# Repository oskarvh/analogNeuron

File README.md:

# analogNeuron
Design doc for an analog neural network (perceptron) built using discrete components.

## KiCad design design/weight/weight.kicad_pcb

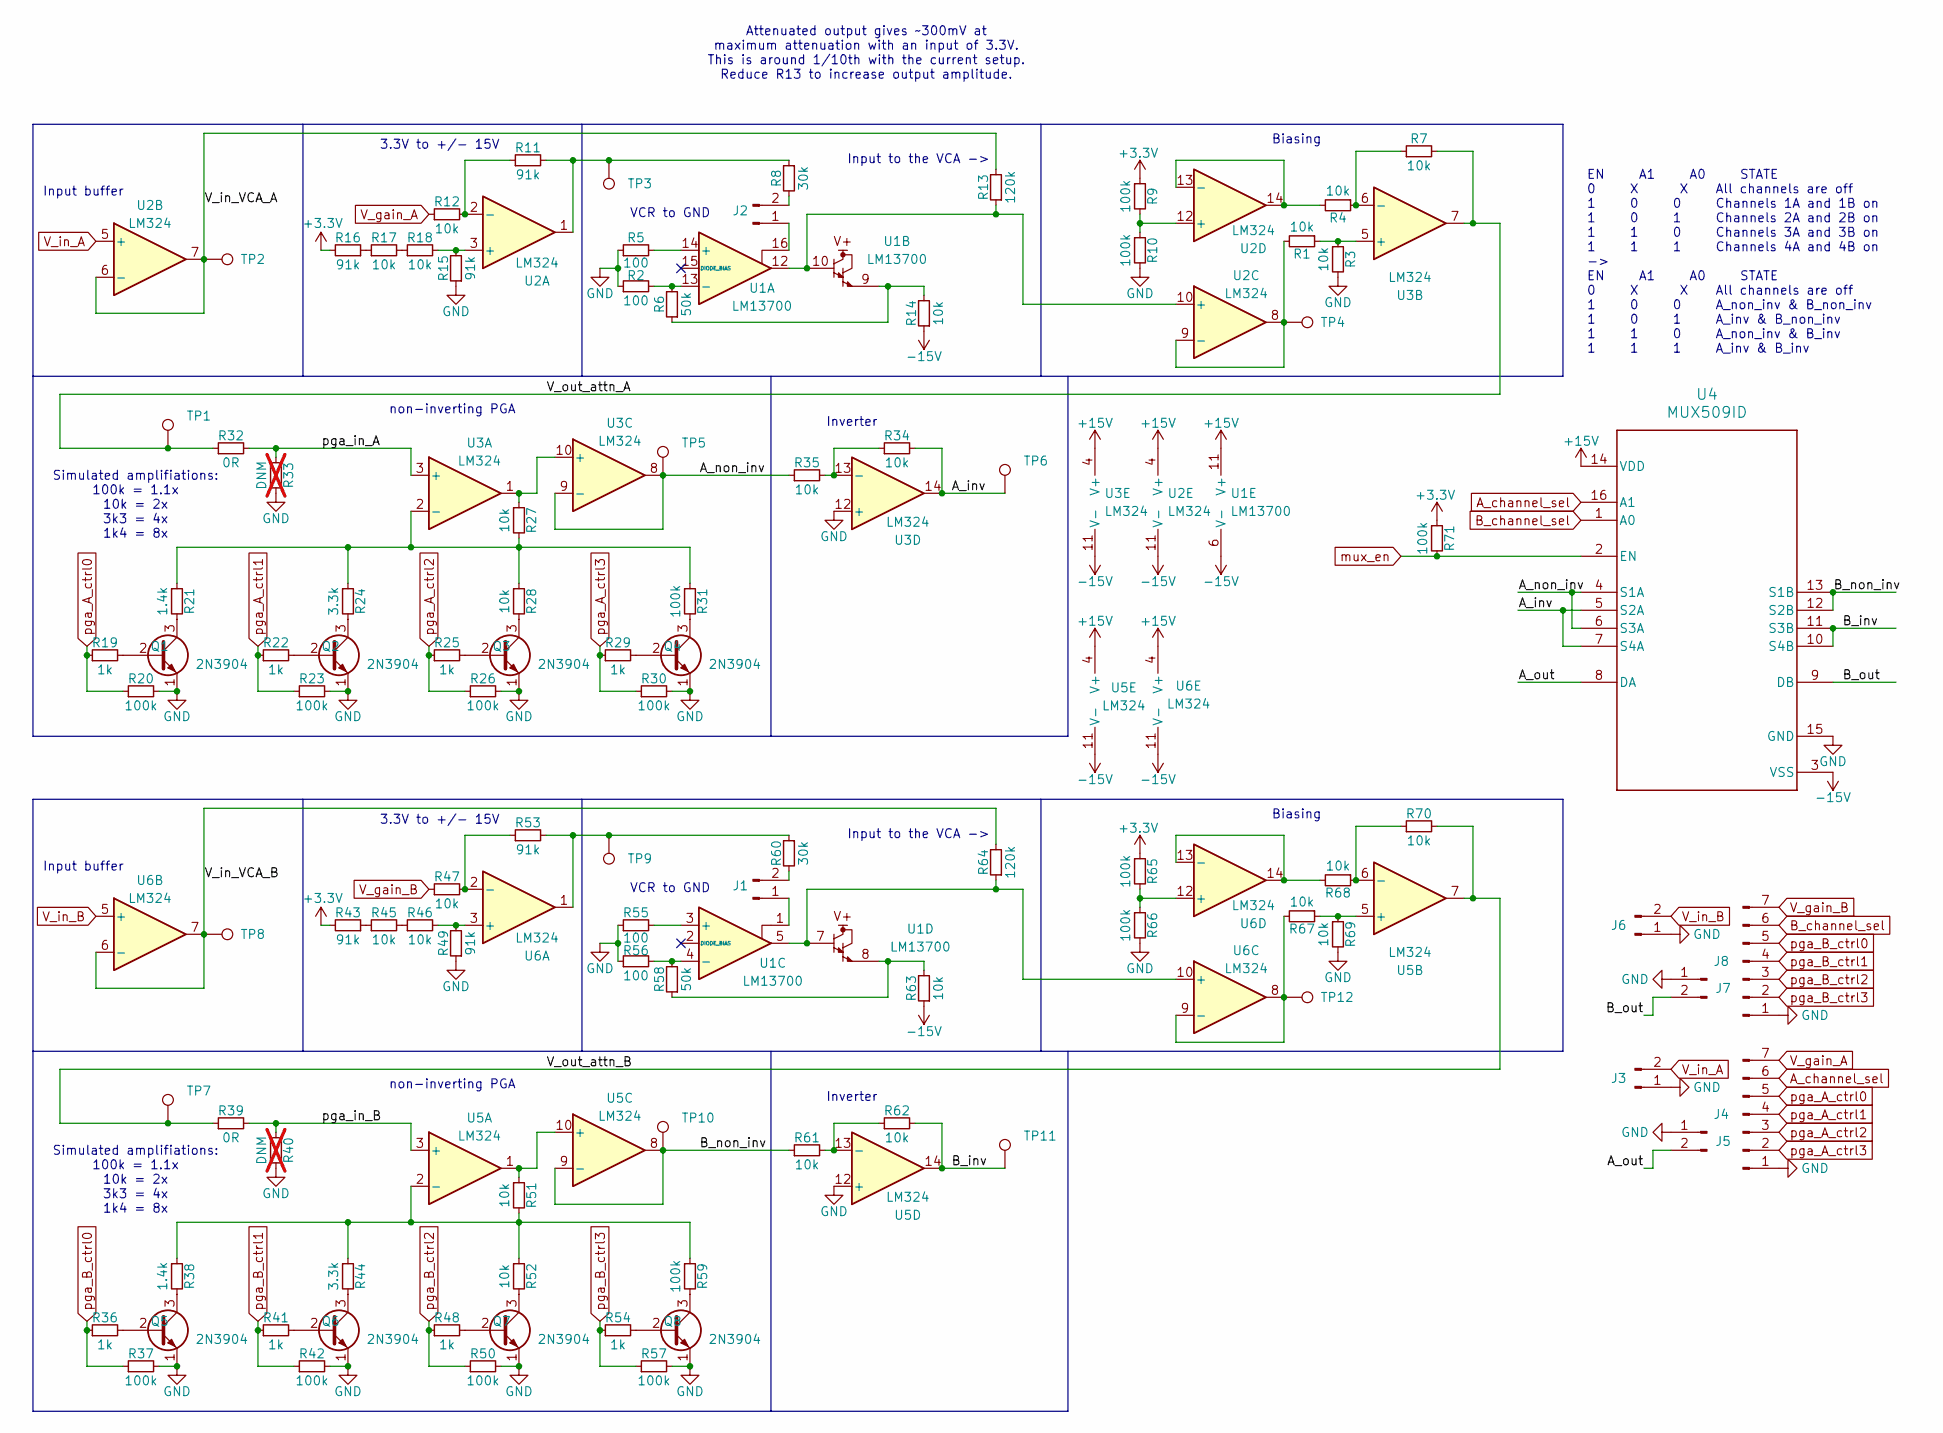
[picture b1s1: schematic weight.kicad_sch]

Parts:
J1, J2, J3, J5, J6, J7: Conn_01x02_Pin; PinHeader_1x02_P2.54mm_Vertical
J4, J8: Conn_01x07_Pin; PinHeader_1x07_P2.54mm_Vertical
Q1, Q2, Q3, Q4, Q5, Q6, Q7, Q8: 2N3904; TO-92_Inline
R1, R3, R4, R7, R12, R14, R17, R18, R27, R28, R34, R35, R45, R46, R47, R51, R52, R61, R62, R63, R67, R68, R69, R70: 10k; R_0402_1005Metric
R2, R5, R55, R56: 100; R_0402_1005Metric
R6, R58: 50k; R_0402_1005Metric
R8, R60: 30k; R_0402_1005Metric
R9, R10, R20, R23, R26, R30, R31, R37, R42, R50, R57, R59, R65, R66, R71: 100k; R_0402_1005Metric
R11, R15, R16, R43, R49, R53: 91k; R_0402_1005Metric
R13, R64: 120k; R_0402_1005Metric
R19, R22, R25, R29, R36, R41, R48, R54: 1k; R_0402_1005Metric
R21, R38: 1.4k; R_0402_1005Metric
R24, R44: 3.3k; R_0402_1005Metric
R32, R39: 0R; R_0402_1005Metric
R33, R40: DNM; R_0402_1005Metric; not fitted
TP1, TP2, TP3, TP4, TP5, TP6, TP7, TP8, TP9, TP10, TP11, TP12: TestPoint; PinHeader_1x01_P2.54mm_Vertical
U1: LM13700; SOIC-16_3.9x9.9mm_P1.27mm
U2, U3, U5, U6: LM324; SOIC127P600X175-14N
U4: MUX509ID; D0016A_N

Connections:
+3.3V: R9.1, R16.2, R43.2, R65.1, R71.1
+15V: U1.11 (V+), U2.4 (V+), U3.4 (V+), U4.14 (VDD), U5.4 (V+), U6.4 (V+)
-15V: R14.1, R63.1, U1.6 (V-), U2.11 (V-), U3.11 (V-), U4.3 (VSS), U5.11 (V-), U6.11 (V-)
/A_inv: R34.2, TP6.1, U3.14, U4.5 (S2A), U4.7 (S4A)
/A_non_inv: R35.1, TP5.1, U3.8, U3.9 (-), U4.4 (S1A), U4.6 (S3A)
/A_out: J5.2, U4.8 (DA)
/B_inv: R62.2, TP11.1, U4.10 (S4B), U4.11 (S3B), U5.14
/B_non_inv: R61.1, TP10.1, U4.12 (S2B), U4.13 (S1B), U5.8, U5.9 (-)
/B_out: J7.2, U4.9 (DB)
/V_in_VCA_A: R13.2, TP2.1, U2.6 (-), U2.7
/V_in_VCA_B: R64.2, TP8.1, U6.6 (-), U6.7
/V_out_attn_A: R7.2, R32.1, TP1.1, U3.7
/V_out_attn_B: R39.1, R70.2, TP7.1, U5.7
/pga_in_A: R32.2, R33.1, U3.3 (+)
/pga_in_B: R39.2, R40.1, U5.3 (+)
A_channel_sel: J4.6, U4.16 (A1)
B_channel_sel: J8.6, U4.1 (A0)
GND: J3.1, J4.1, J5.1, J6.1, J7.1, J8.1, Q1.1 (E), Q2.1 (E), Q3.1 (E), Q4.1 (E), Q5.1 (E), Q6.1 (E), Q7.1 (E), Q8.1 (E), R2.1, R3.2, R5.1, R10.2, R15.1, R20.2, R23.2, R26.2, R30.2, R33.2, R37.2, R40.2, R42.2, R49.1, R50.2, R55.1, R56.1, R57.2, R66.2, R69.2, U3.12 (+), U4.15 (GND), U5.12 (+)
unnamed: J1.1, U1.1
unnamed: J1.2, R60.2
unnamed: J2.1, U1.16
unnamed: J2.2, R8.2
unnamed: Q1.2 (B), R19.2
unnamed: Q1.3 (C), R21.2
unnamed: Q2.2 (B), R22.2
unnamed: Q2.3 (C), R24.2
unnamed: Q3.2 (B), R25.2
unnamed: Q3.3 (C), R28.2
unnamed: Q4.2 (B), R29.2
unnamed: Q4.3 (C), R31.2
unnamed: Q5.2 (B), R36.2
unnamed: Q5.3 (C), R38.2
unnamed: Q6.2 (B), R41.2
unnamed: Q6.3 (C), R44.2
unnamed: Q7.2 (B), R48.2
unnamed: Q7.3 (C), R52.2
unnamed: Q8.2 (B), R54.2
unnamed: Q8.3 (C), R59.2
unnamed: R8.1, R11.2, TP3.1, U2.1
unnamed: R6.1, R14.2, U1.9
unnamed: R16.1, R17.1
unnamed: R17.2, R18.1
unnamed: R43.1, R45.1
unnamed: R45.2, R46.1
unnamed: R53.2, R60.1, TP9.1, U6.1
unnamed: R58.1, R63.2, U1.8
unnamed: R5.2, U1.14 (+)
unnamed: R2.2, R6.2, U1.13 (-)
unnamed: R55.2, U1.3 (+)
unnamed: R56.2, R58.2, U1.4 (-)
unnamed: R15.2, R18.2, U2.3 (+)
unnamed: R11.1, R12.2, U2.2 (-)
unnamed: R13.1, U1.10, U1.12, U2.10 (+)
unnamed: R1.2, TP4.1, U2.8, U2.9 (-)
unnamed: R9.2, R10.1, U2.12 (+)
unnamed: R4.2, U2.13 (-), U2.14
unnamed: R21.1, R24.1, R27.2, R28.1, R31.1, U3.2 (-)
unnamed: R1.1, R3.1, U3.5 (+)
unnamed: R4.1, R7.1, U3.6 (-)
unnamed: R27.1, U3.1, U3.10 (+)
unnamed: R34.1, R35.2, U3.13 (-)
unnamed: R38.1, R44.1, R51.2, R52.1, R59.1, U5.2 (-)
unnamed: R67.1, R69.1, U5.5 (+)
unnamed: R68.1, R70.1, U5.6 (-)
unnamed: R51.1, U5.1, U5.10 (+)
unnamed: R61.2, R62.1, U5.13 (-)
unnamed: R46.2, R49.2, U6.3 (+)
unnamed: R47.2, R53.1, U6.2 (-)
unnamed: R64.1, U1.5, U1.7, U6.10 (+)
unnamed: R67.2, TP12.1, U6.8, U6.9 (-)
unnamed: R65.2, R66.1, U6.12 (+)
unnamed: R68.2, U6.13 (-), U6.14
V_gain_A: J4.7, R12.1
V_gain_B: J8.7, R47.1
V_in_A: J3.2, U2.5 (+)
V_in_B: J6.2, U6.5 (+)
mux_en: R71.2, U4.2 (EN)
pga_A_ctrl0: J4.5, R19.1, R20.1
pga_A_ctrl1: J4.4, R22.1, R23.1
pga_A_ctrl2: J4.3, R25.1, R26.1
pga_A_ctrl3: J4.2, R29.1, R30.1
pga_B_ctrl0: J8.5, R36.1, R37.1
pga_B_ctrl1: J8.4, R41.1, R42.1
pga_B_ctrl2: J8.3, R48.1, R50.1
pga_B_ctrl3: J8.2, R54.1, R57.1

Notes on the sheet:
Input to the VCA ->
3.3V to +/- 15V
Inverter
VCR to GND
Biasing
Simulated amplifiations: 100k = 1.1x 10k = 2x 3k3 = 4x 1k4 = 8x
Attenuated output gives ~300mV at maximum attenuation with an input of 3.3V. This is around 1/10th with the current setup. Reduce R13 to increase output amplitude.
EN A1 A0 STATE 0 X X All channels are off 1 0 0 Channels 1A and 1B on 1 0 1 Channels 2A and 2B on 1 1 0 Channels 3A and 3B on 1 1 1 Channels 4A and 4B on -> EN A1 A0 STATE 0 X X All channels are off 1 0 0 A_non_inv & B_non_inv 1 0 1 A_inv & B_non_inv 1 1 0 A_non_inv & B_inv 1 1 1 A_inv & B_inv
non-inverting PGA
Input buffer

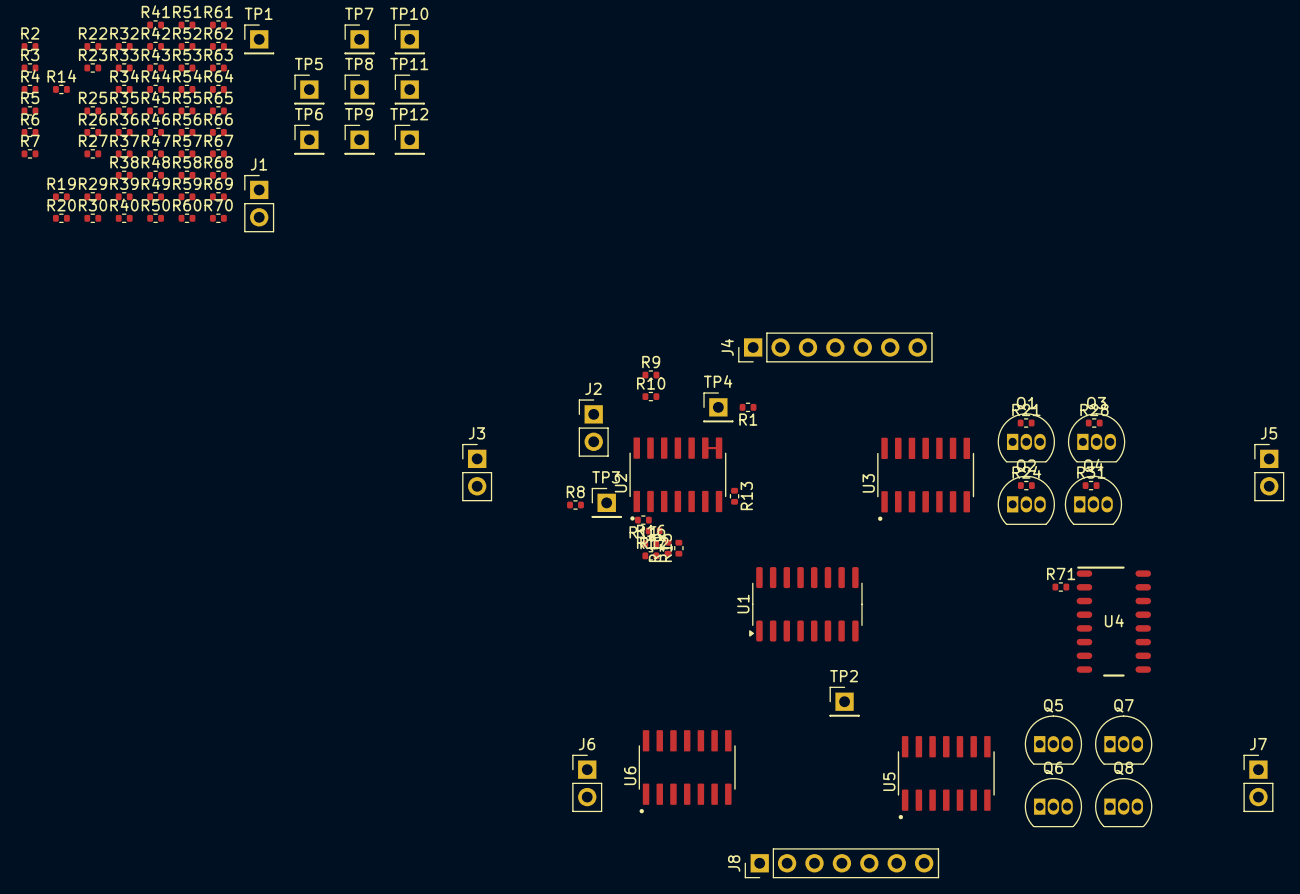
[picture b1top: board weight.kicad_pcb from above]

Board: 2 copper layers, 105 parts (0 on the bottom side), 85 nets.

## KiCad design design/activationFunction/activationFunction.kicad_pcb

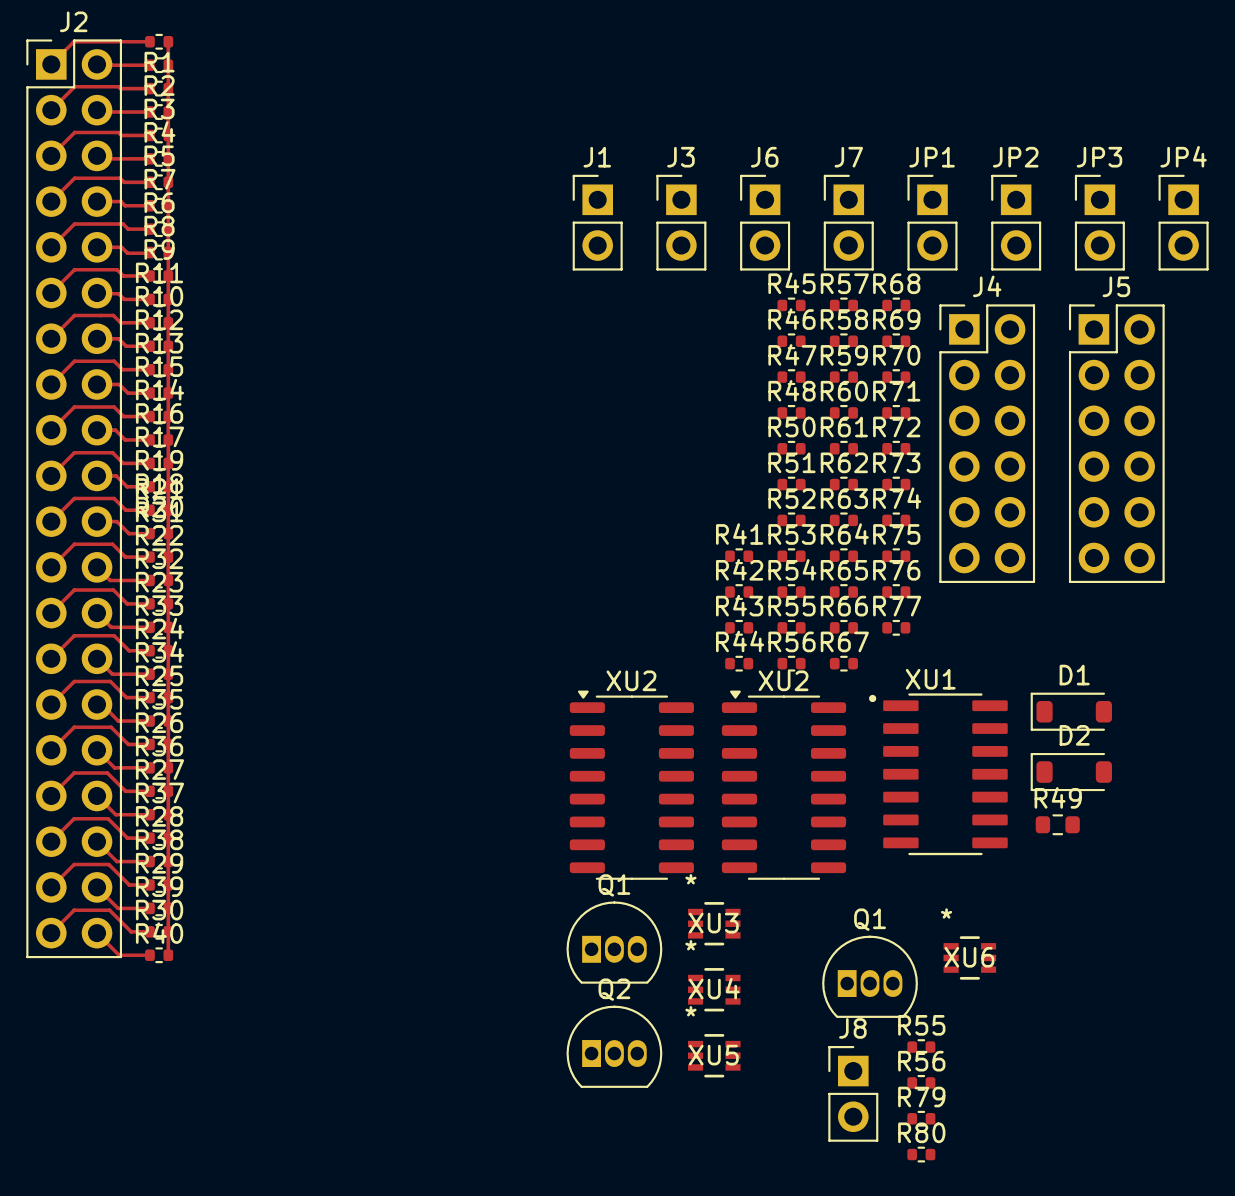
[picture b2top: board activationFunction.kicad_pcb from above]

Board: 2 copper layers, 105 parts (0 on the bottom side), 89 nets.

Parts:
D1, D2: 1N4148WGW; D_SOD-123
J1, J3, J6, J7, J8: Conn_01x02_Pin; PinHeader_1x02_P2.54mm_Vertical
J2: Conn_02x20_Counter_Clockwise; PinHeader_2x20_P2.54mm_Vertical
J4, J5: Conn_02x06_Counter_Clockwise; PinHeader_2x06_P2.54mm_Vertical
JP1, JP2, JP3, JP4: Jumper_2_Small_Open; PinHeader_1x02_P2.54mm_Vertical
Q1, Q1#2, Q2: 2N3904; TO-92_Inline
R1, R2, R3, R4, R5, R6, R7, R8, R9, R10, R11, R12, R13, R14, R15, R16, R17, R18, R19, R20, R21, R22, R23, R24, R25, R26, R27, R28, R29, R30, R31, R32, R33, R34, R35, R36, R37, R38, R39, R40, R41, R46, R50, R54, R55, R55#2, R56, R56#2, R57, R58, R60, R61: 100k; R_0402_1005Metric
R42, R51, R52, R53, R59: 1k; R_0402_1005Metric
R43: 35k; R_0402_1005Metric
R44: 5k; R_0402_1005Metric
R45, R63, R64, R66, R69, R70, R71, R72, R73: 10k; R_0402_1005Metric
R47, R48, R79, R80: 33k; R_0402_1005Metric
R49: 500k; R_0603_1608Metric
R62: 15k; R_0402_1005Metric
R65, R67, R68, R74, R75, R76: 91k; R_0402_1005Metric
R77: 0; R_0402_1005Metric
XU1: LM324; SOIC127P600X175-14N
XU2, XU2#2: LM13700; SOIC-16_3.9x9.9mm_P1.27mm
XU3, XU4, XU5, XU6: SSM6N7002CFU_LF; SOT-363 US6_TOS

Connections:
0: J3.1, J4.4, J4.9, J5.4, J5.9, J6.1, J7.1, R41.1, R49.1, R55.1, R68.1, R75.1, XU2.10, XU2.12, XU2#2.10, XU2#2.12, XU3.5, XU6.5
3.3V: J4.3, J4.10, J5.3, J5.10, R70.1, R71.1
+15V: D2.2 (A), J4.1, J4.12, J5.1, J5.12, Q1.3 (C), Q2.3 (C), XU1.4 (V+), XU2.11 (V+), XU2#2.11 (V+)
-15V: J4.2, J4.11, J5.2, J5.11, R51.2, R52.2, R53.2, R63.1, R64.1, XU1.11 (V-), XU2.6 (V-), XU2#2.6 (V-), XU5.5, XU6.2
/V_bias_l: J7.2, R73.1
/V_diff_n: Q2.2 (B), R48.2, XU3.3 (4)
/V_diff_out: Q2.1 (E), R54.1
/V_diff_p: R47.2, XU3.6 (1)
/V_in: R1.1, R2.1, R3.1, R4.1, R5.1, R6.1, R7.1, R8.1, R9.1, R10.1, R11.1, R12.1, R13.1, R14.1, R15.1, R16.1, R17.1, R18.1, R19.1, R20.1, R21.2, R22.2, R23.2, R24.2, R25.2, R26.2, R27.2, R28.2, R29.2, R30.2, R31.2, R32.2, R33.2, R34.2, R35.2, R36.2, R37.2, R38.2, R39.2, R40.2, R58.2, XU1.3 (+)
/V_out: J3.2, R56.2, R56#2.2, XU1.7
/V_sink: J1.2, XU4.3 (4)
/V_slope_l: J6.2, R66.1
/V_sum: R42.1, R43.2, R44.1, R45.1, R46.1, XU1.1
/V_sum_bias: R43.1, XU2.5, XU2.7, XU2#2.5, XU2#2.7, XU3.2
/out_bias: Q1.2 (B), R80.2, XU6.3 (4)
unnamed: D1.2 (A), D2.1 (K)
unnamed: D1.1 (K), Q1#2.3 (C), R47.1, R48.1, R50.1, R79.1, R80.1
unnamed: J1.1, R77.1, XU3.1 (3), XU3.4 (6)
unnamed: J2.1, R1.2
unnamed: J2.2, R2.2
unnamed: J2.3, R3.2
unnamed: J2.4, R4.2
unnamed: J2.5, R5.2
unnamed: J2.6, R7.2
unnamed: J2.7, R6.2
unnamed: J2.8, R8.2
unnamed: J2.9, R9.2
unnamed: J2.10, R11.2
unnamed: J2.11, R10.2
unnamed: J2.12, R12.2
unnamed: J2.13, R13.2
unnamed: J2.14, R15.2
unnamed: J2.15, R14.2
unnamed: J2.16, R16.2
unnamed: J2.17, R17.2
unnamed: J2.18, R19.2
unnamed: J2.19, R18.2
unnamed: J2.20, R20.2
unnamed: J2.21, R21.1
unnamed: J2.22, R31.1
unnamed: J2.23, R22.1
unnamed: J2.24, R32.1
unnamed: J2.25, R23.1
unnamed: J2.26, R33.1
unnamed: J2.27, R24.1
unnamed: J2.28, R34.1
unnamed: J2.29, R25.1
unnamed: J2.30, R35.1
unnamed: J2.31, R26.1
unnamed: J2.32, R36.1
unnamed: J2.33, R27.1
unnamed: J2.34, R37.1
unnamed: J2.35, R28.1
unnamed: J2.36, R38.1
unnamed: J2.37, R29.1
unnamed: J2.38, R39.1
unnamed: J2.39, R30.1
unnamed: J2.40, R40.1
unnamed: J8.1, XU6.1 (3), XU6.4 (6)
unnamed: J8.2, XU5.6 (1)
unnamed: JP1.1 (A), JP2.1 (A), JP3.1 (A), JP4.1 (A), R41.2, XU1.2 (-)
unnamed: JP1.2 (B), R42.2
unnamed: JP2.2 (B), R44.2
unnamed: JP3.2 (B), R45.2
unnamed: JP4.2 (B), R46.2
unnamed: Q1#2.2 (B), R50.2
unnamed: Q1.1 (E), Q1#2.1 (E), R57.1
unnamed: R60.1, R63.2, XU2.8, XU2#2.8
unnamed: R61.2, R64.2, XU2.9, XU2#2.9
unnamed: R62.1, XU2.1, XU2.16, XU2#2.1, XU2#2.16
unnamed: R67.1, R69.2
unnamed: R69.1, R70.2
unnamed: R71.2, R72.1
unnamed: R72.2, R74.1
unnamed: R54.2, R55.2, R56#2.1, XU1.5 (+)
unnamed: R55#2.2, R56.1, R57.2, XU1.6 (-)
unnamed: R67.2, R68.2, XU1.10 (+)
unnamed: R65.1, R66.2, XU1.9 (-)
unnamed: R74.2, R75.2, XU1.12 (+)
unnamed: R73.2, R76.1, XU1.13 (-)
unnamed: R59.1, R60.2, XU2.4 (-), XU2.14 (+), XU2#2.4 (-), XU2#2.14 (+)
unnamed: R59.2, R61.1, XU2.3 (+), XU2.13 (-), XU2#2.3 (+), XU2#2.13 (-)
unnamed: R49.2, XU4.2, XU4.5, XU4.6 (1), XU5.2
unnamed: R51.1, XU4.1 (3)
unnamed: R52.1, XU4.4 (6)
unnamed: R53.1, XU5.1 (3)
unnamed: R79.2, XU6.6 (1)
V_bias: J4.5, J4.8, J5.5, J5.8, R58.1, R76.2, XU1.14
V_slope: J4.6, J4.7, J5.6, J5.7, R62.2, R65.2, XU1.8

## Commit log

2025-02-17 Activation function now simulated
2025-02-18 Added some more designs from the doc. activation function and VCA done, still need PGA to complete weight
2025-02-23 Finished the weight design
